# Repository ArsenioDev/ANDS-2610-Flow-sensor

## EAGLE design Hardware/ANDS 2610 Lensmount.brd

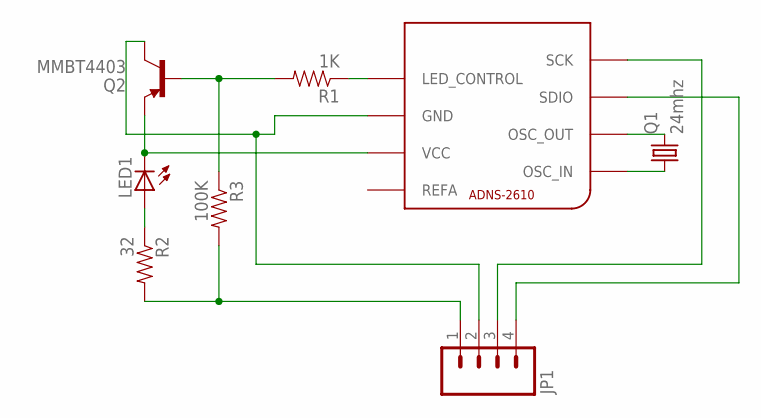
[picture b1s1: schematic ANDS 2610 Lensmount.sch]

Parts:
JP1: M04PTH; 1X04
LED1: LED3MM
Q1: 24mhz; HC49/S
Q2: MMBT4403; SOT23-3
R1: 1K; 1206
R2: 32; 1206
R3: 100K; 1206
U$1: ADNS-2610

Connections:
unnamed: Q2.1 (B), R1.2, R3.1
unnamed: R1.1, U$1.LED_CONTROL
unnamed: JP1.2, Q2.3 (C), U$1.GND
unnamed: JP1.1, R2.2, R3.2
unnamed: LED1.K (C), Q2.2 (E), U$1.VCC
unnamed: LED1.A, R2.1
unnamed: Q1.2, U$1.OSC_OUT
unnamed: Q1.1, U$1.OSC_IN
unnamed: JP1.3, U$1.SCK
unnamed: JP1.4, U$1.SDIO

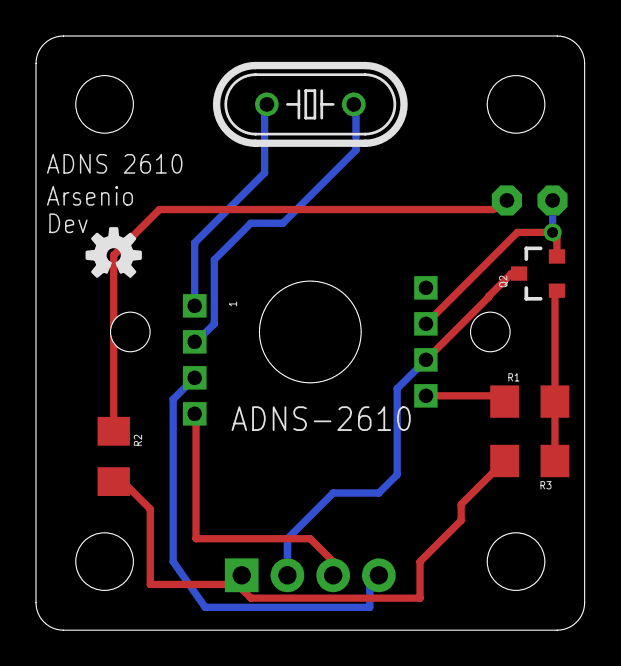
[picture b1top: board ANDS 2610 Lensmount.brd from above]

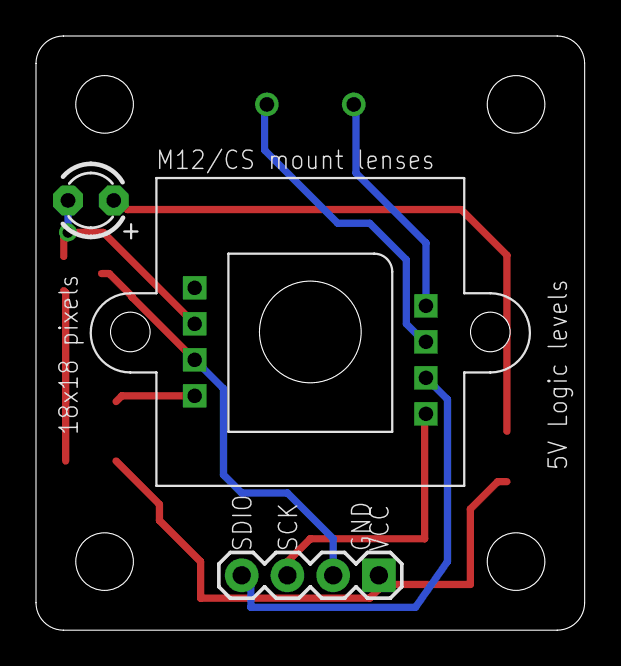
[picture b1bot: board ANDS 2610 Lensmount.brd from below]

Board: 2 copper layers, 30.5 x 33.0 mm, 9 parts (2 on the bottom side), 10 nets.

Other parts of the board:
U$2: OSHW-LOGO-S

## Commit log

2016-01-23 :confetti_ball: Added .gitattributes & .gitignore files
2016-01-23 init
    f
2016-01-23 Fixed trace
    Had a trace crossing the Crystal leads

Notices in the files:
parts and their libraries:
SparkFun-Connectors: Licensing: Creative Commons ShareAlike 4.0 International - https://creativecommons.org/licenses/by-sa/4.0
